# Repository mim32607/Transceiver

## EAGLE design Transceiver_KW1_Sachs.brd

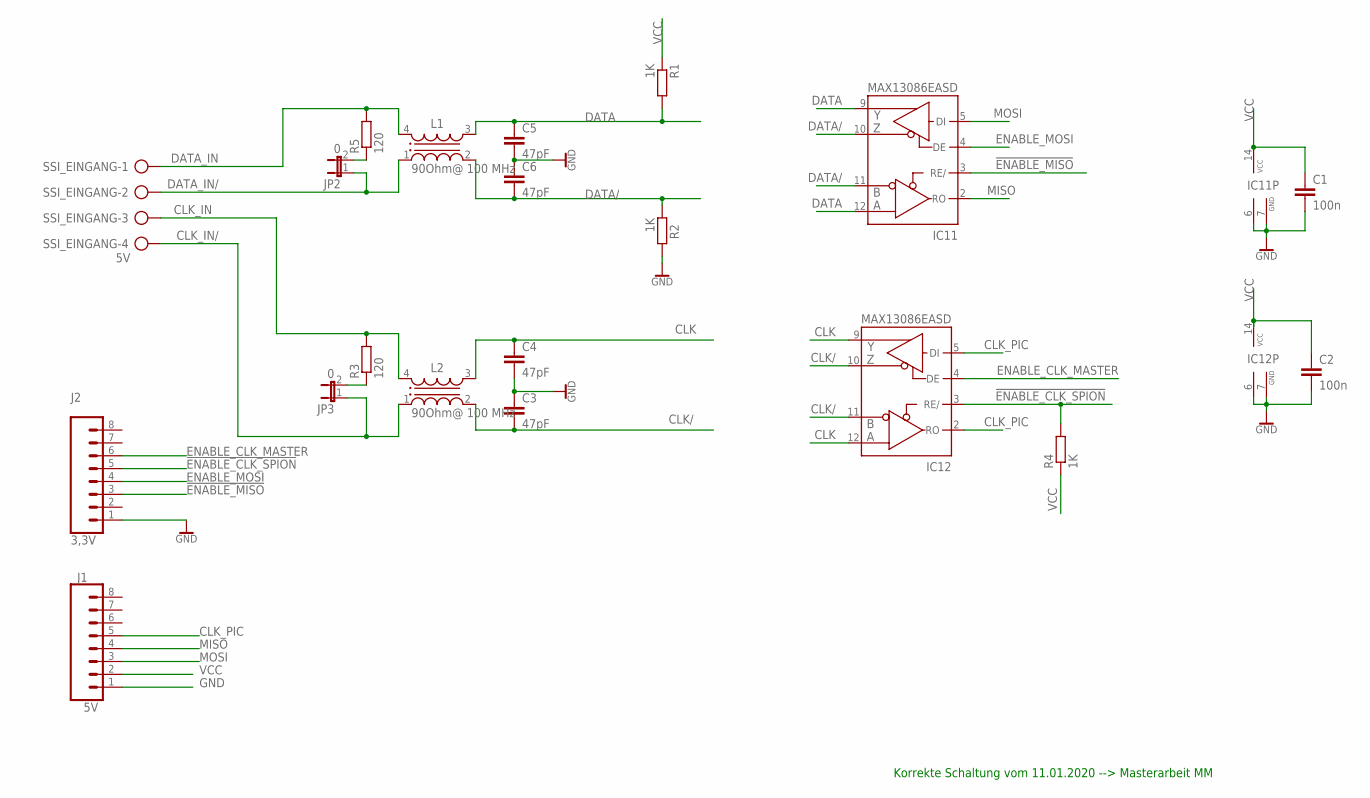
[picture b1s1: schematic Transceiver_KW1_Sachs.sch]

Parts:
C1, C2: 100n; C0603
C3, C4, C5, C6: 47pF; C0603
IC11, IC12: MAX13086EASD; SO14
J1: 5V; 1X08
J2: 3,3V; 1X08
JP2, JP3: 0; JP1
L1, L2: 90Ohm@ 100 MHz; WE-CNSW_0805
R1, R2, R4: 1K; R0603
R3, R5: 120; R0603
SSI_EINGANG: 5V; AK500/4-H

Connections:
!ENABLE_CLK_SPION!: IC12.3 (RE/), J2.5, R4.2
!ENABLE_MISO!: IC11.3 (RE/), J2.3
CLK: C4.1, IC12.9 (Y), IC12.12 (A), L2.3 (2)
CLK/: C3.2, IC12.10 (Z), IC12.11 (B), L2.2 (3)
CLK_IN: L2.4 (1), R3.2, SSI_EINGANG.3
CLK_IN/: JP3.1, L2.1 (4), SSI_EINGANG.4
CLK_PIC: IC12.2 (RO), IC12.5 (DI), J1.5
DATA: C5.1, IC11.9 (Y), IC11.12 (A), L1.3 (2), R1.2
DATA/: C6.2, IC11.10 (Z), IC11.11 (B), L1.2 (3), R2.1
DATA_IN: L1.4 (1), R5.2, SSI_EINGANG.1
DATA_IN/: JP2.1, L1.1 (4), SSI_EINGANG.2
ENABLE_CLK_MASTER: IC12.4 (DE), J2.6
ENABLE_MOSI: IC11.4 (DE), J2.4
GND: C1.2, C2.2, C3.1, C4.2, C5.2, C6.1, IC11.6 (GND), IC11.7 (GND), IC12.6 (GND), IC12.7 (GND), J1.1, J2.1, R2.2
MISO: IC11.2 (RO), J1.4
MOSI: IC11.5 (DI), J1.3
unnamed: JP2.2, R5.1
unnamed: JP3.2, R3.1
VCC: C1.1, C2.1, IC11.14 (VCC), IC12.14 (VCC), J1.2, R1.1, R4.1

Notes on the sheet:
Korrekte Schaltung vom 11.01.2020 --> Masterarbeit MM

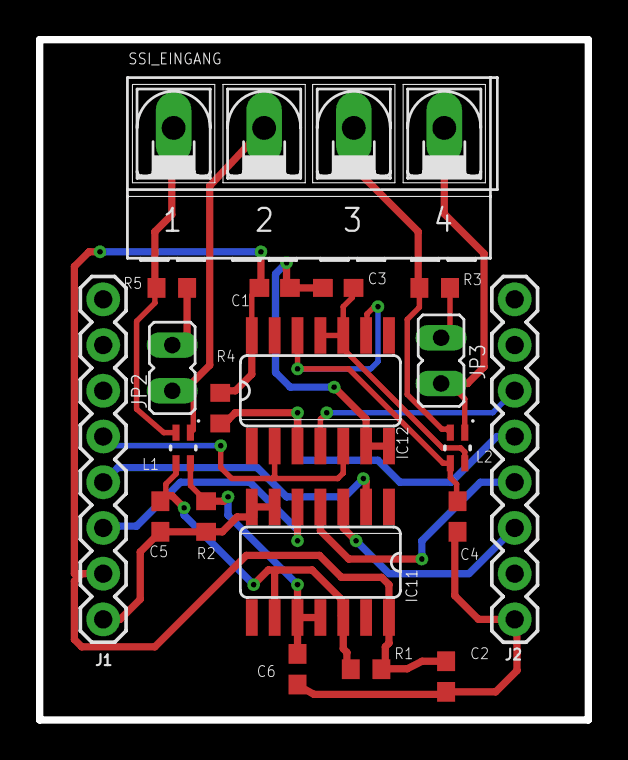
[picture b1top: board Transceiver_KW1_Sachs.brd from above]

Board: 2 copper layers, 30.5 x 37.8 mm, 20 parts (0 on the bottom side), 19 nets.

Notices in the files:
parts and their libraries:
SparkFun-Connectors: Licensing: Creative Commons ShareAlike 4.0 International - https://creativecommons.org/licenses/by-sa/4.0
Eagle_WE-CNSW: Copyright: Würth Elektronik
